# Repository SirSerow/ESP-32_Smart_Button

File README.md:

# Smart Button with ESP32

## Overview
This project is a **Smart Button** based on the ESP32 microcontroller. The purpose of the project is to make PC operation easy and understandable for older people. With the help of the button, users can trigger predefined actions on their computer, such as opening applications, changing settings, or sending messages.The device is designed to function as a wireless communication interface for triggering predefined actions. The button integrates **ESP-NOW**, **Wi-Fi**, **battery monitoring**, and an **OLED display** for visual feedback. The project includes both **firmware** (ESP32-side) and a **software application** (computer-side) based on C# to control the computer running Windows OS.

## Features
- **ESP-NOW Wireless Communication:** Enables low-latency, direct device-to-device communication.
- **OLED Display (SSD1351, SPI):** Provides visual feedback for the button's status and received commands.
- **Battery Monitoring:** Uses ADC calibration to estimate battery percentage.
- **External Power Detection:** Automatically detects external power and adjusts behavior.
- **Sleep Mode for Power Saving:** The device enters deep sleep when inactive for a certain period.
- **Configurable Timeout Alerts:** Notifies when the button loses connection.
- **ESP-NOW & UART Communication:** Supports both wireless peer-to-peer messaging and wired serial communication.
- **Computer-Side Application:** Monitors the button's status, performs actions on the computer and has an user interface for setting up button actions.

## Hardware Components
- **ESP32 Development Board**
- **SSD1351 OLED Display (SPI)**
- **Push Button**
- **Battery & Charging Circuit**
- **I2C Communication (SDA: GPIO21, SCL: GPIO22)**
- **Status LED (GPIO14)**
- **External Power Detection (GPIO39)**

## Circuit Diagram
The detailed schematic of the **Smart Button** circuit can be found in the [doc folder](./doc/Board_Schematic.pdf).

## PCB Layout
The project includes a fully designed two-layer PCB for manufacturing. Components are placed exclusevily on top layer to lower the assebly cost and simplify the repairs. For similar reason, in terms of component enclosure type, the preference was given to SMD components. Layout files are available in the hardware folder.

<div align="center" style="margin-top: 30px; margin-bottom: 20px;">
    <b>Top View:</b><br>
    <div style="margin-top: 20px;">
        
    </div>
</div>

<div align="center" style="margin-top: 30px; margin-bottom: 20px;">
    <b>Bottom View:</b><br>
    <div style="margin-top: 20px;">
        
    </div>
</div>

<div align="center" style="margin-top: 30px; margin-bottom: 20px;">
    <b>Side View:</b><br>
    <div style="margin-top: 20px;">
        
    </div>
</div>

## Software Features
The computer-side application for the Smart Button enhances its usability by allowing users to configure and automate various actions triggered by the button press. The application runs as a Windows GUI-based tool, providing an intuitive interface for setting up and managing button actions. 

Since the application is designed to run on Windows, it is developed using C# and .NET Framework. The application communicates with the Smart Button via a serial connection (UART). The framework and communication were chosen to be simple and easy to use and to fit older systems with limited resources.

There are two ways to connect the Smart Button to the computer:
1. **Wired Connection:** The Smart Button is connected to the computer via a USB cable, and the application communicates with the button over a serial port.
2. **Wireless Connection:** The Smart Button communicates with the computer over a wireless connection using the ESP32's ESP-NOW protocol. ESP32 reciever is connected to the computer via USB cable. 

#### **Key Features**
1. **Serial Communication with the Smart Button**
   - Automatically detects the Smart Button via **USB serial ports**.
   - Monitors and logs communication between the button and the PC.
   - Detects button presses and relays corresponding actions.

2. **Configurable Button Actions**
   - Users can assign different actions to the button, such as:
     - **Opening a website (link)**
     - **Making a phone call**
     - **Sending an email**
     - **Launching an application**
   - Each button press executes the assigned function immediately.

3. **Quick Action Setup & Profiles**
   - **User-defined actions** can be assigned to different buttons in the UI.
   - **Multiple configuration profiles** allow quick switching between different use cases.
   - **Preloaded default configurations** available on first launch.

4. **Real-Time Device Status Monitoring**
   - Displays the **current connection status** of the button.
   - Tracks the **last received ping** from the button to ensure connectivity.
   - Shows **battery status** if supported by the Smart Button.

5. **Graphical User Interface (GUI)**
   - Provides a **Windows Forms-based UI** for easy configuration.
   - Displays **icons** for different action types (browser, call, email, application).
   - Supports **customization of button labels and images**.

6. **System Tray Integration**
   - Runs **minimized in the system tray** to remain active in the background.
   - Right-click system tray menu allows quick access to settings and exit options.

7. **Automatic Device Detection**
   - Scans **available COM ports** and attempts to find the button.
   - Provides **visual indicators** if the button is successfully detected.

8. **Error Handling & Debugging Tools**
   - Logs device connection attempts and failures.
   - Displays **error messages** for missing configurations.
   - Allows **manual device selection** if automatic detection fails.

9. **Windows Registry & Configuration Management**
   - Reads and writes **configuration settings** using the **Windows Registry**.
   - Saves **user preferences** such as the default action and last-used settings.

10. **Power & Sleep Monitoring**
   - Tracks **button inactivity** to optimize power usage.
   - Monitors the **last button press time** to prevent unintended actions.
   - Supports **automatic sleep mode handling** if the button is inactive.

<div align="center" style="margin-bottom: 20px;">
    <b>Main App Window:</b><br>
    
</div>

<div align="center" style="margin-bottom: 20px;">
    <b>Action Pick:</b><br>
    
</div>

<div align="center" style="margin-bottom: 20px;">
    <b>User Guide:</b><br>
    
</div>

## Firmware Overview
The firmware is written using ESP-IDF and structured as follows:

### Key Components:
1. **ESP-NOW Communication**
   - Registers peers for sending/receiving messages.
   - Handles status updates and custom triggers.

2. **Battery & Power Management**
   - Reads battery voltage via ADC.
   - Detects external power and adjusts behavior accordingly.

3. **Sleep Mode**
   - Enters deep sleep mode if inactive for 60 seconds.
   - Wakes up when the button is pressed.

4. **Display Management**
   - Uses LovyanGFX for rendering text/icons.
   - Displays battery percentage, status updates, and alerts.

5. **Button Task**
   - Detects button presses and sends wireless data via ESP-NOW.
   - Provides visual feedback on the OLED screen.

6. **UART Communication**
   - Sends debug messages and status updates via UART.
   - Receives commands from the computer-side application.

7. **Configuration & Settings**
   - Stores default actions and settings in NVS.
   - Allows changing actions via ESP-NOW messages.

8. **Error Handling & Debugging**
   - Logs errors, warnings, and status updates.
   - Provides detailed information for troubleshooting.

## Mechanical Design

The **Smart Button** enclosure is a **custom-designed mechanical housing** that protects internal components while ensuring ease of use. The enclosure consists of **three main parts**:

1. **Top Enclosure** – Contains a **large window** to accommodate the display, ensuring clear visibility.  
2. **Bottom Enclosure** – Designed to securely hold the **PCB and battery**, optimizing space for a compact form factor.  
3. **Button** – A **large, colorful, and easy-to-press button**, providing a tactile and responsive experience.

| Smart Button | Receiver |
|-------------|----------|
|   |   |

#### **Design & Manufacturing**
- The enclosure was designed using **Fusion 360** for precise integration with the PCB and battery.
- The entire assembly is **optimized for 3D printing**, allowing for easy prototyping and customization.
- The button design ensures **smooth actuation** while preventing accidental presses.

#### **Assembly & Fastening**
- Assembly is **simple and efficient**, requiring only **three bolts** to securely hold the enclosure together.
- The button fits into the **top enclosure**, allowing for **firm yet smooth movement** when pressed.

| Main Body Assembly | Receiver Assembly |
|-------------------|------------------|
|   |  |

#### **Customization & Modifications**
- The **3D printable design** allows for easy modifications, such as:
  - Adjusting dimensions for alternative PCB layouts.
  - Customizing button colors and shapes for different applications.
  - Adding ventilation or additional mounting options.

## Usage
The **Smart Button** software provides an intuitive way to configure and use the button for different actions. 
This section explains how to install, configure, and use the software.

#### **1. Installation**
- Download the latest release of the **Smart Button** software.
- Extract the files to a preferred directory.
- Run the **setup.exe** from MagicButtonSetup/Release folder.
- Follow the installation wizard to complete the setup.
- Start the application from the desktop shortcut.

#### **2. Initial Setup**
- On the first launch, the application will prompt you to set up **default actions**.
- Select the desired action for button presses:
  - **Call**: Enter a phone number and contact name.
  - **Email**: Enter an email address and subject.
  - **Application**: Choose an application to launch.
  - **Website**: Enter a URL for quick access.
- Save the settings, and the software will remember them for future use.

#### **3. Connecting the Smart Button**
- Plug the **Smart Button** or receiver device into a USB port.
- The application will attempt to **auto-detect the device**.
- If the device is not detected:
  - Open the **Settings** panel and manually select the COM port.
- Once connected, the UI will show the device **status and connection logs**.

#### **4. Configuring Button Actions**
- Navigate to the **Button Setup** panel.
- Assign actions to different button presses:
  - **Short Press** → Quick Action (e.g., Open a website)
  - **Long Press** → Secondary Action (e.g., Make a call)
  - **Double Press** → Custom Action (e.g., Launch an application)
- Click **Save** to apply the changes.

#### **5. Using the Smart Button**
- **Single press** executes the assigned action.
- **Holding the button** triggers an alternative action.
- **Double-clicking** performs a special function (e.g., emergency contact).
- The system tray icon will show notifications about the current action.

#### **6. Monitoring Status & Logs**
- The **Main Dashboard** displays:
  - **Device Connection Status**
  - **Last Button Press Timestamp**
  - **Current Battery Level** (if supported)
  - **Recent Logs & Debug Messages**
- If the button loses connection, the software will display a **warning**.

#### **7. System Tray & Background Mode**
- The application can be minimized to the **system tray** for background operation.
- Right-click the tray icon to:
  - **Open Settings**
  - **Reconnect the Button**
  - **Exit the Application**

#### **8. Resetting & Troubleshooting**
- If the button stops responding:
  - Check the **USB connection**.
  - Restart the application and ensure the device is detected.
  - Use the **Reset Device** option in the settings.
  - Check device **battery level** and **power source**.

#### **9. Power Management & Sleep Mode**
- If the button is inactive for a long period:
  - It will enter **power-saving mode**.
  - The application will notify the user if a connection is lost.
  - The button can be **reactivated** with a press.
- The software monitors **battery percentage** and alerts the user if charging is needed.

## Future Enhancements
- **BLE Integration** for mobile applications.
- **Multi-button Pairing** for grouped communication.
- **Cloud Connectivity** via MQTT for IoT applications.

## Known issues
- **Battery Monitoring:** The battery percentage calculation may not be accurate due to voltage fluctuations.
- **PCB Design:** The butto component placement and connection has to be reconsidered, currently connection has to be manually fixed. The PCB layout may require further optimization for mass production.
- **ESP-NOW Communication:** The wireless communication may be affected by interference or distance limitations.

## License
This project is open-source under the **MIT License**.

## Acknowledgements
Special thanks to **Espressif** for the **ESP32** platform and **LovyanGFX** for display handling. The PCB design was based on [ESP32-DevKit-Lipo](https://github.com/OLIMEX/ESP32-DevKit-LiPo/tree/master) by Olimex, original files were changed to adapt to the project requirements.

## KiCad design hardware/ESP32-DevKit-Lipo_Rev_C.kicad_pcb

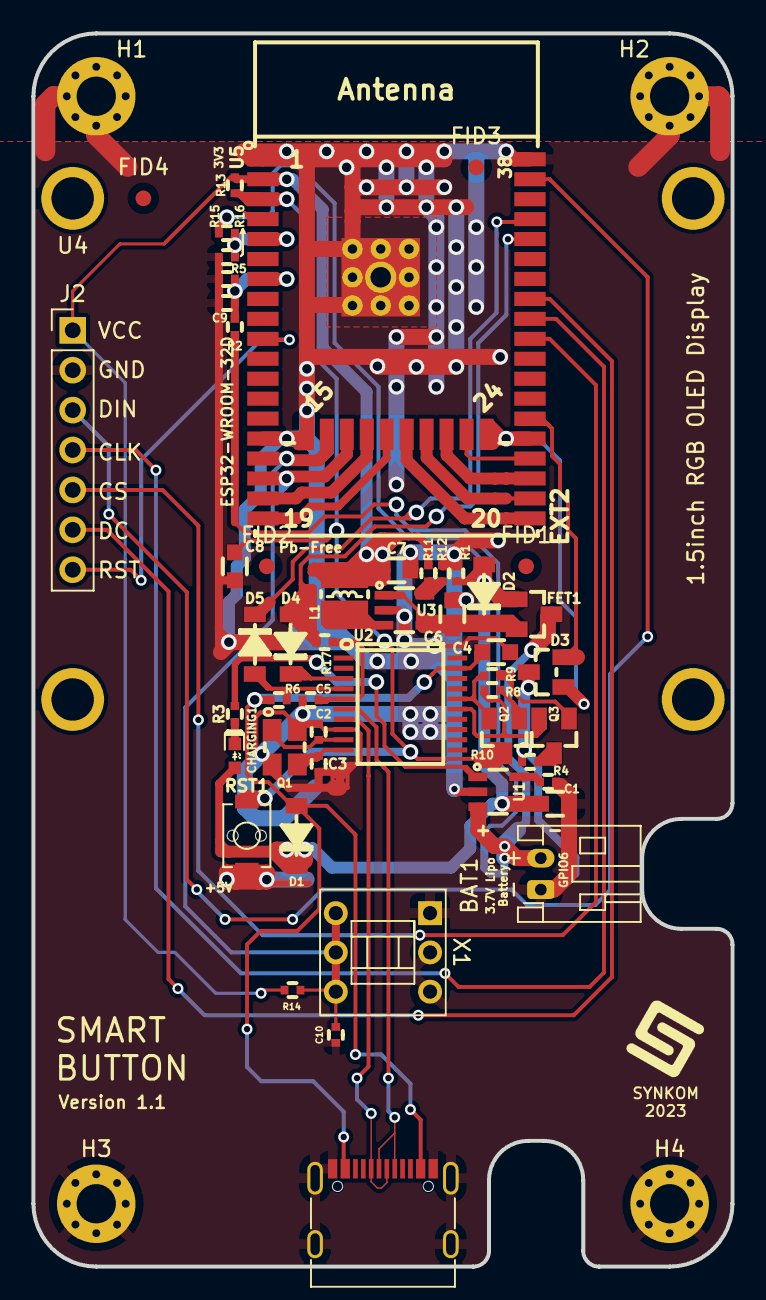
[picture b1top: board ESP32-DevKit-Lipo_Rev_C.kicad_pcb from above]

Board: 2 copper layers, 44.5 x 78.5 mm, 56 parts (1 on the bottom side), 37 nets.

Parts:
BAT1: DW02S; JST_PH_S2B-PH-K_1x02_P2.00mm_Horizontal
C1, C4, C6, C7: 22uF/6.3V/20%/X5R/C0603; C_0603_5MIL_DWS
C2, C3: 27pF/50V/5%/C0G/C0402; C_0402_5MIL_DWS
C5, C9, C10: 100nF/10V/10%/X7R/C0402; C_0402_5MIL_DWS
C8: 1uF/10V/10%/X5R/C0603; C_0603_5MIL_DWS
CHARGING1: LED/YELLOW/0603; LED_0603_KA
D1, D2, D4, D5: 1N5819S4/SOD123; SOD-123_1C-2A_KA
D3: BAT54C(SOT23-3); SOT23-3
D_Com1: TESTPAD; TESTPAD_40-ROUND
FET1: WPM2015-3/TR; SOT23
FID1, FID2, FID3, FID4: Fiducial; Fiducial_1mm_Mask2mm
H1, H2, H3, H4: MountingHole_Pad; MountingHole_2.5mm_Pad_Via
J1: USB_C_Receptacle_USB2.0; USB_C_Receptacle_G-Switch_GT-USB-7010ASV
J2: Conn_01x07; PinHeader_1x07_P2.54mm_Vertical
L1: 2.2uH/1.5A/DCR=72mR/20%/3.00x3.00x1.50mm/CD32(NR3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; CD32
Q1: Q12MHz/20pF/10ppm/4P/3.2x2.5mm; TSX-3.2x2.5mm_GND(3)
Q2, Q3: BC817-40(SOT23); SOT23
R1, R6, R13, R14, R17: 10k/R0402; R_0402_5MIL_DWS
R2, R5, R16: 470k/R0402; R_0402_5MIL_DWS
R3, R4, R8, R9: 2.2k/R0402; R_0402_5MIL_DWS
R10: 220R/R0402; R_0402_5MIL_DWS
R11: 100k/R0402; R_0402_5MIL_DWS
R12: 22k/1%/R0402; R_0402_5MIL_DWS
R15: 220k/R0402; R_0402_5MIL_DWS
RST1: IT-1185AU2-160G-G-TR; IT1185AU2_V2
U1: BL4054B-42TPRN(SOT23-5); SOT-23-5
U2: CH340T(SSOP20W); SSOP-20W
U3: SY8089AAAC(SOT23-5); SOT-23-5
U4: Waveshare 1.5inch OLED display Module, 128x128 pixels
U5: ESP32-WROOM-32D-4MB; ESP32-WROVER_MODULE
X1: XKB8080-W

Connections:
+3V3: C7.1, J2.1, L1.2, R11.2, R13.1, R14.1, U5.2 (VDD33(3V3))
+5V: C1.1, CHARGING1.2 (A), D1.1 (K), D2.2 (A), FET1.1, R1.1, R15.1, U1.4 (VCC)
/+5V_USB: C4.1, D1.2 (A), J1.A4 (VBUS), J1.A9 (VBUS), J1.B4 (VBUS), J1.B9 (VBUS), R6.1, U2.19 (VCC)
/D_Com: D3.3 (CC), D_Com1.1 (Pad), R10.2
/ESP_EN: C8.1, Q2.3 (C), R13.2, RST1.1, U5.3 (EN)
/GPI35: C9.2, R2.2, R5.1, U5.7 (GPI35/ADC1_CH7/RTC_GPIO5)
/GPI39\SENSOR_VN: R15.2, R16.1, U5.5 (GPI39/SENSOR_VN/ADC1_CH3/ADC_H/RTC_GPIO3)
/GPIO0: D3.2 (A2), U5.25 (GPIO0/ADC2_CH1/TOUCH1/RTC_GPIO11/CLK_OU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)
/GPIO1\U0TXD: D5.1 (K), U5.35 (GPIO1/U0TXD/CLK_OUT3/EMAC_RXD2)
/GPIO2: D3.1 (A1), U5.24 (GPIO2/ADC2_CH2/TOUCH2/RTC_GPIO12/HSPIWP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)
/GPIO3\U0RXD: D4.2 (A), R17.2, U5.34 (GPIO3/U0RXD/CLK_OUT2)
/GPIO5: J2.5, U5.29 (GPIO5/VSPICS0/HS1_DATA6/EMAC_RX_CLK)
/GPIO13: C10.1, R14.2, U5.16 (GPIO13/ADC2_CH4/TOUCH4/RTC_GPIO14/MTCK/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), X1.4, X1.5, X1.6
/GPIO18: J2.4, U5.30 (GPIO18/VSPICLK/HS1_DATA7)
/GPIO19: J2.6, U5.31 (GPIO19/VSPIQ/U0CTS/EMAC_TXD0)
/GPIO23: J2.3, U5.37 (GPIO23/VSPID/HS1_STROBE)
/GPIO25: J2.7, U5.10 (GPIO25/DAC_1/ADC2_CH8/RTC_GPIO6/EMAC_RX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)
GND: BAT1.1, C1.2, C2.2, C3.2, C4.2, C5.2, C6.2, C7.2, C8.2, C9.1, C10.2, H1.1, H2.1, H3.1, H4.1, J1.A1 (GND), J1.A12 (GND), J1.B1 (GND), J1.B12 (GND), J1.S1 (SHIELD), J2.2, Q1.3 (case), R1.2, R4.2, R5.2, R12.2, R16.2, RST1.2, U1.2 (GND), U2.8 (GND), U3.2 (GND), U5.1 (GND), U5.15 (GND), U5.38 (GND), U5.39 (THERMAL_PAD), X1.1, X1.2, X1.3
unnamed: CHARGING1.1 (K), R3.1
unnamed: C6.1, D2.1 (K), FET1.2, U3.1 (EN), U3.4 (IN)
unnamed: D4.1 (K), U2.3 (TXD)
unnamed: D5.2 (A), R6.2, U2.4 (RXD)
unnamed: Q2.1 (B), R8.2
unnamed: Q2.2 (E), R9.1, U2.16 (RTS#)
unnamed: Q3.1 (B), R9.2
unnamed: Q3.3 (C), R10.1
unnamed: Q3.2 (E), R8.1, U2.15 (DTR#)
unnamed: R3.2, U1.1 (CHRGb)
unnamed: R4.1, U1.5 (PROG)
unnamed: J1.A6 (D+), J1.B6 (D+), U2.6 (UD+)
unnamed: J1.A7 (D-), J1.B7 (D-), U2.7 (UD-)
unnamed: C5.1, R17.1, U2.5 (V3)
unnamed: C2.1, Q1.1, U2.9 (XI)
unnamed: C3.1, Q1.2, U2.10 (XO)
unnamed: R11.1, R12.1, U3.5 (FB)
unnamed: L1.1, U3.3 (LX)
VBAT: BAT1.2, FET1.3, R2.1, U1.3 (VBAT)

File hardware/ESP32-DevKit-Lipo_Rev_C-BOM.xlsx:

Comment | Designator | Footprint
220R R0402 | R10 | R0402
2.2k R0402 | R3,R4,R8,R9 | R0402
10k R0402 | R1,R6,R13,R17 | R0402
49.9k 1% R0402 | R12 | R0402
220k R0402 | R11,R15 | R0402
470k R0402 | R2,R5,R16 | R0402
2.2uH 1.5A DCR=72mR 20% 3.00x3.00x1.50mm CD32(NR3015T2R2M) | L1 | CD32
27pF 50V 5% C0G C0402 | C2,C3 | C0402
100nF 10V 10% X7R C0402 | C5,C9 | C0402
1uF 10V 10% X5R C0603 | C8 | C0603
22uF 6.3V 20% X5R C0603 | C4,C1,C6,C7 | C0603
LED YELLOW 0603 | CHARGING1 | LED_0603
BAT54C(SOT23-3) | D3 | SOT23-3
1N5819S4 SOD123 | D1,D2,D4,D5 | SOD-123
BC817-40(SOT23) | Q2,Q3 | SOT23
WPM2015-3 TR | FET1 | SOT23
BL4054B-42TPRN(SOT23-5) | U1 | SOT-23-5
CH340T(SSOP20W) | U2 | SSOP-20W
SY8089AAAC(SOT23-5) | U3 | SOT-23-5
Q12MHz 20pF 10ppm 4P 3.2x2.5mm | Q1 | TSX-3.2x2.5mm
MISB-SWMM-5B-LF(USB_MICRO) | USB-UART1 | MISB-SWMM-5B_LF
IT-1185AU2-160G-G-TR | RST1 | IT1185AU2
DW02S | BAT1 | DW02S
HN1x19 | EXT1,EXT2 | HN1x19
ESP32-WROOM-32D-4MB | U5 | ESP32-MODULE_Universal
Opened | BAT_PWR_E1, BAT_SENS_E1, PWR_SENS_E1 | SJ
NA R0402 | R7 | R0402

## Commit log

2025-02-04 Initial push
2025-02-05 Updated readme, removed useless data
2025-02-05 Updated readme, added drawings
2025-02-05 Working on readme fix
2025-02-05 Fixed readme and updated picture extension name
2025-02-05 Updated extension to fix the application window image
